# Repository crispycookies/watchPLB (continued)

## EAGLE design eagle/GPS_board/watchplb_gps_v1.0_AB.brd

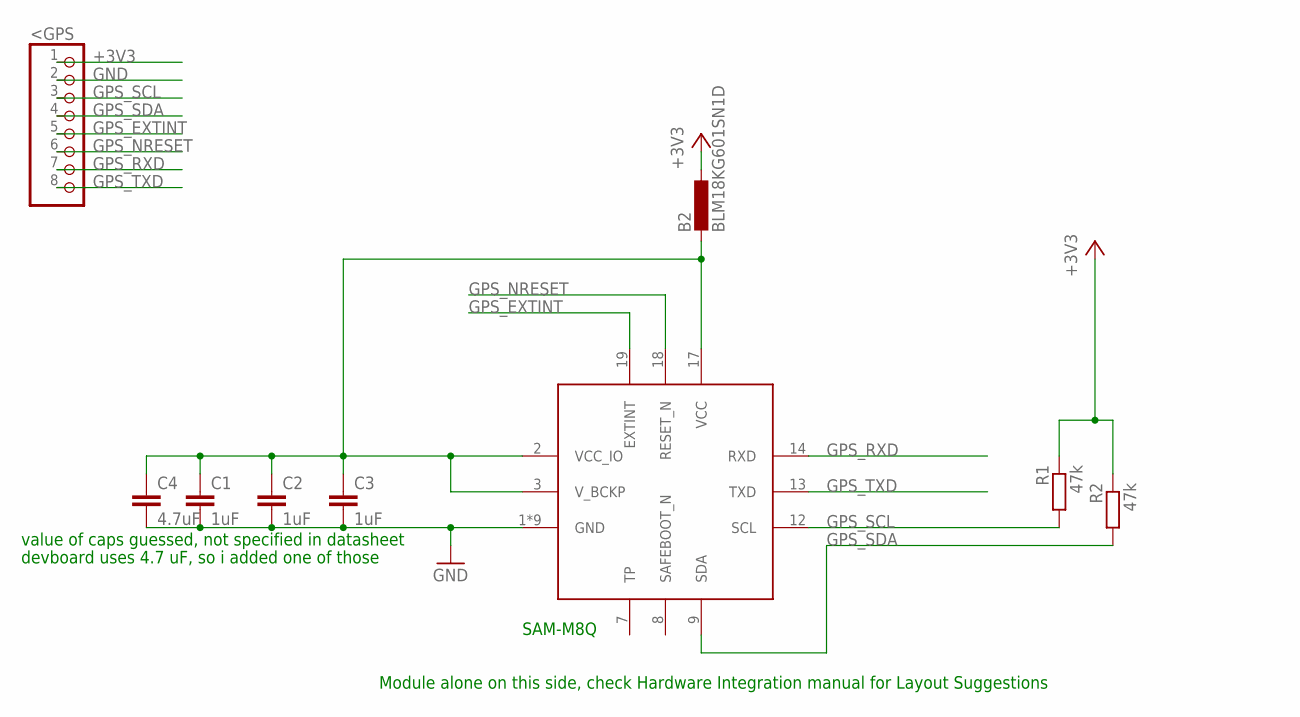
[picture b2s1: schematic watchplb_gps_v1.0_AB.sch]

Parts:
<GPS: PINHD-1X8; 1X08
B2: BLM18KG601SN1D; L0603
C1, C2, C3: 1uF; C0805
C4: 4.7uF; C0805
IC1: SAM-M8Q
R1, R2: 47k; M0805

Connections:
+3V3: <GPS.1, B2.1, R1.1, R2.1
GND: <GPS.2, C1.2, C2.2, C3.2, C4.2, IC1.1 (GND), IC1.4 (GND), IC1.5 (GND), IC1.6 (GND), IC1.10 (GND), IC1.11 (GND), IC1.15 (GND), IC1.16 (GND), IC1.20 (GND)
GPS_EXTINT: <GPS.5, IC1.19 (EXTINT)
GPS_NRESET: <GPS.6, IC1.18 (RESET_N)
GPS_RXD: <GPS.7, IC1.14 (RXD)
GPS_SCL: <GPS.3, IC1.12 (SCL), R1.2
GPS_SDA: <GPS.4, IC1.9 (SDA), R2.2
GPS_TXD: <GPS.8, IC1.13 (TXD)
unnamed: B2.2, C1.1, C2.1, C3.1, C4.1, IC1.2 (VCC_IO), IC1.3 (V_BCKP), IC1.17 (VCC)

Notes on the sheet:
Module alone on this side, check Hardware Integration manual for Layout Suggestions
value of caps guessed, not specified in datasheet
devboard uses 4.7 uF, so i added one of those
SAM-M8Q

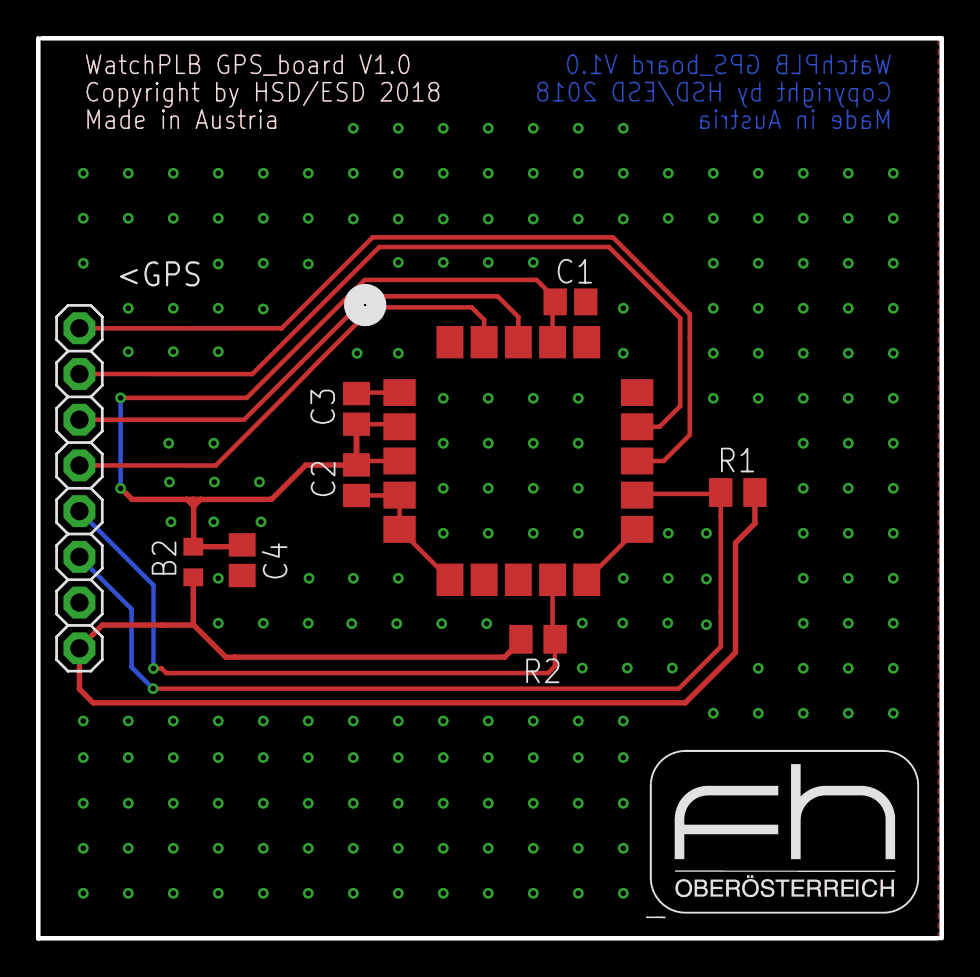
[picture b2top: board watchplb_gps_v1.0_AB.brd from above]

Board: 2 copper layers, 50.2 x 50.0 mm, 10 parts (0 on the bottom side), 9 nets.

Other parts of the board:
U$1: FH_LOGO_050

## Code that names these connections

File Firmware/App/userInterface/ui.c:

/**
 **************************
 * @file    ui.c
 * @author  Michael Neuhofer
 * @version V1.0
 * @date    18.12.2018
 * @brief   user interface module
 **************************
 */

#include <stdbool.h>

#include "ui.h"
#include "led_driver.h"
#include "sysclock_driver.h"
#include "vibrator_driver.h"
#include "key.h"
#include "emergencyCall.h"
#include "battery.h"
#include "adc.h"
#include <stdbool.h>


typedef enum {
	UI_Idle, UI_Waiting, UI_SendLocation, UI_Sleepmode
} UIstates;

UIstates UIstate = UI_Idle;
static bool isSleepmode = false;
static const TIME ledtimercd = 10;
static REGISTER ledreg = 0x0F;

const uint8_t battery_100 = 80;
const uint8_t battery_80 = 60;
const uint8_t battery_60 = 40;
const uint8_t battery_40 = 20;
const uint8_t battery_20 = 0;

const uint16_t limiter = 1000;
static uint16_t counter = 0;

void UI_UpdateBattery() {
	// Check Battery state via ADC
	uint8_t battery = battery_status();

	if (battery > battery_100 ) {
		led_on(led_pa4);
		led_on(led_pa5);
		led_on(led_pa6);
		led_on(led_pa7);
		led_on(led_pc4);
	} else if (battery > battery_80) {
		led_off(led_pa4);
		led_on(led_pa5);
		led_on(led_pa6);
		led_on(led_pa7);
		led_on(led_pc4);
	} else if (battery > battery_60) {
		led_off(led_pa4);
		led_off(led_pa5);
		led_on(led_pa6);
		led_on(led_pa7);
		led_on(led_pc4);
	} else if (battery > battery_40) {
		led_off(led_pa4);
		led_off(led_pa5);
		led_off(led_pa6);
		led_on(led_pa7);
		led_on(led_pc4);
	} else if (battery >= battery_20) {
		led_off(led_pa4);
		led_off(led_pa5);
		led_off(led_pa6);
		led_off(led_pa7);
		led_on(led_pc4);
	} else {
		_Error_Handler("statebatteryerror", 222);
	}

}

void UI_TurnLEDsOff() {
	led_off(led_pa4);
	led_off(led_pa5);
	led_off(led_pa6);
	led_off(led_pa7);
	led_off(led_pc4);
	led_off(led_pc5);
	led_off(led_pb0);
	led_off(led_pb1);
	led_off(led_pb2);
}

void UI_CrazyLEDs() {
	led_timer_start();
	led_action_time(led_pa4, ledreg);
	led_action_time(led_pa5, ledreg);
	led_action_time(led_pa6, ledreg);
	led_action_time(led_pa7, ledreg);
	led_action_time(led_pc4, ledreg);
//led_action_time(led_pc5,ledreg);
	led_action_time(led_pb0, ledreg);
	led_action_time(led_pb1, ledreg);
	led_action_time(led_pb2, ledreg);
//led_timer_stop();
}

HAL_StatusTypeDef UI_Init() {

	KEY_Init();

	led_init();
	battery_init();

	led_timer_init(ledtimercd);
//vibrator_init(GPIOA,15);
	UIstate = UI_Idle;

	return HAL_OK;
}

HAL_StatusTypeDef UI_Update() {


	if(counter >= limiter){
		UI_UpdateBattery();
		counter = 0;
	}
	counter++;


	switch (UIstate) {
	case UI_Idle: {

		UIstate = UI_Waiting;
		break;
	}
	case UI_Waiting: {

		led_on(led_pb1);

		if (KEY_Get(BTN_1) == GPIO_PIN_SET) {
			// Sleepmode
			UIstate = UI_Sleepmode;
		} else if (KEY_Get(BTN_2) == GPIO_PIN_SET) {
			// activate Bluetooth here ////////////////////////////////////////////////////////////////
			led_on(led_pb0); /////////////////////////////TEST PURPOSE
			UIstate = UI_Waiting;

		} else if (KEY_Get(BTN_3) == GPIO_PIN_SET) {
			if (KEY_Get(BTN_4) == GPIO_PIN_SET) {
				//SOS
				UIstate = UI_SendLocation;
			}
		}

		// show the battery status via LEDs
		//UI_UpdateBattery();

		break;
	}
	case UI_SendLocation: {
		//vibrator_on();
		// call SOS function

		EMC_SetEmergency(EMC_State_Emergency);

		//vibrator_off();
		led_on(led_pb2); /////////////////////////////TEST PURPOSE

		UIstate = UI_Waiting;
		break;
	}
	case UI_Sleepmode: {
		if (isSleepmode != true) {
			UI_TurnLEDsOff();
			isSleepmode = true;
			SystemClock_SleepMode_Config();
			// indicates Sleepmode
			led_on(led_pc5);
		}

		if (KEY_Get(BTN_2) == GPIO_PIN_SET || KEY_Get(BTN_3) == GPIO_PIN_SET
				|| KEY_Get(BTN_4) == GPIO_PIN_SET) {
			SystemClock_UnSleepMode_Config();
			UIstate = UI_Waiting;
			isSleepmode = false;
			led_off(led_pc5);
		}
		break;
	}
	default: {
		//errorhandler makes all LEDs go crazy
		_Error_Handler("stateerror", 222);
	}
	}

	return HAL_OK;
}

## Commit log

2018-03-06 Add .gitignore
2018-03-06 first version of specification
2018-04-03 initial upload schematic
2018-04-03 Add new directory
2018-04-03 initial commit schematic
2018-04-03 initial upload board
2018-04-03 Added Pflichtenheft Directory
2018-04-03 Uploaded Pflichtenheft.pdf
2018-04-03 Upload Pflichtenheft.tex
2018-04-03 antenna_calc
2018-04-03 Firmware init
2018-04-03 Updated Pflichtenheft.tex
2018-04-03 Updated Pflichtenheft.pdf
2018-04-06 added folder to git ignore
2018-04-17 added pdf version
2018-04-17 added testpoints, moved pins so pb11 is free to make it pin kompatibel to another prozessor with more power
2018-04-17 created directory structure
2018-04-17 no message
2018-04-18 finished directory structure
2018-04-18 finished makefile
2018-04-18 created specification
2018-04-18 added com interface
2018-04-18 mein benutzereigenschaften und hardwareschnittstellen
2018-04-18 Punkt 5 erledigt
2018-04-18 punkt 2.2 und 4 done
2018-04-19 imported olgas specification changes
2018-04-19 Added Pflichtenheft
2018-04-19 Replaced Specification as it failed last time
2018-04-19 pflichenheft änderungen: alles bei punkt 2, ausser 2.1.3, 2.1.4 und 2.2 und punkt 3
2018-04-20 meine änderungen
2018-04-20 merged specifications
2018-04-20 Removed Contradictoriness
2018-04-20 added PCB acronym list
2018-04-24 added wakeup pin support and page for psu (empty atm)
2018-04-24 added auto-generated BOM
2018-04-24 added gitignore for eagle
2018-04-24 include stm32l0xx_hal_conf.h in all files
2018-04-24 added mouser numbers for most products, changed switches to smd
2018-04-24 changed mosfet to one with sot23 footprint
2018-04-24 added new mosfet to bom
2018-04-24 Template for EVA
2018-04-24 Upload Lights Template for EVA
2018-05-06 started on uart implementation
2018-05-08 USB-VCOM generated with cubemx and changed to send useful message
2018-05-08 added VCOM usb port with protection
2018-05-09 implemented most uart routines. TODO: DMA and interrupts
2018-05-15 fixed lowercase app directory to uppercase App
2018-05-15 added RF transmitter (amp still missing) and generated new pdf of schematic for tobi
2018-05-15 added rf amp and sma connector, reorganised for better pdf page ordering
2018-05-16 fixed makefile to also work on Linux
2018-05-16 Untested LED- Driver-Compileable
2018-05-16 Untested Led- Driver- Full Project
2018-05-16 Fixed Directory Struct
2018-05-16 Removed Folders
2018-05-16 added battery protection circuit
2018-05-22 added calculations as excel file and battery charge circuitry in schematic
2018-05-22 Added Vibrator and removed uselessenum in led driver
2018-05-26 added linear regulators + calculations for them, exported parts as library, generated new pdf
2018-05-26 added 4.7uF to gps module because the devboard does that.
2018-05-27 added dma interrupt module
2018-05-27 worked on uart driver: worked on dma implementation
2018-05-28 compile uart module instead of usart, compile uart extension
2018-05-28 configure interrupt priority
2018-05-28 implemented start transmission and interrupts and
2018-05-29 implemented receiver
2018-05-29 added error returns added uart receive idle line detection
2018-05-29 added missing names + new pdf
2018-05-29 switched to cubeMx cmsis driver
2018-05-29 small schematic changes, started with layout
2018-06-05 keyTreiber getestet und funktionsfählig
    adc not finished so far
2018-06-05 added some datasheets and continued with layout
2018-06-05 Fixed Led- Driver. Timer may be too Fast
2018-06-05 Fixed Led Driver Constants
2018-06-05 continued layout
2018-06-06 added necessary components
2018-06-06 enable dma interrupts
2018-06-06 reset data of all handlers to prevent errors by initial values
2018-06-06 enable dma clock and USART interrupt
2018-06-06 set usart instance before initialisation
2018-06-06 clear correct interrupt
2018-06-06 clear initial idle interrupt and enable idle interrupts
2018-06-06 addec test routine for the uart module
2018-06-12 layout v1 fertig
2018-06-12 Final LED- Driver Rework
    Added Documentation in Code and fixed Interrupt Bug
2018-06-12 Doxygen Documentation
    Finalized Doxygen Documentation for Vibrator/forceFeedback
2018-06-12 adc / key fertig
2018-06-12 added text and fh logo
2018-06-12 watchdog implementiert nicht getestet
2018-06-19 SPI Driver Untested
    Untested and Probably doesnt work either...
2018-06-19 changes requested by armin brandl
2018-06-19 SPI Driver Untested and Merged
2018-06-19 fixed uart
2018-06-22 weitere Änderungen von Armin Brandl
2018-07-11 von Armin überarbeitete Version der GPS-Platine
2018-07-11 Änderungen laut Besprechung mit Armin (soweit ich mich erinnern kann, ist schon ne woche her)
2018-07-11 SPI Driver Tested on APUS
2018-07-17 fixed copy paste error
2018-07-18 kleine Änderungen laut email mit Armin, veraltete Dateien entfernt, gerber generiert
2018-07-18 modified gitignore so gerber files get committed too
2018-07-19 added comments and additional checks against null- pointer
2018-07-19 added comments
2018-07-20 started BOM
2018-07-26 BOMs finished, requesting feedback from Armin Brandl
2018-07-27 changes to BOM as requested by Armin Brandl
2018-07-27 small changes
2018-09-04 Added Files for use with SmtAssistant
2018-09-24 Removed NUL- File
2018-09-24 Untested Bugfixed for SPI
2018-09-29 Marked received Parts on BOM
2018-09-29 Noticed that I forgot to apply the Calculations for Linear Voltage Regulators to eagle, fixed this
2018-10-02 Formular for test PLB
2018-10-03 removed unnecessary extern inclusions
2018-10-03 deleted file 'NUL'
2018-10-03 fixed directories: removed debug folder, merged app folder into App
2018-10-05 Proposal for BLE- Interface
2018-10-05 Removed Useless Array in SPI.c
2018-10-09 adc+watchdog fertig und kommentiert
2018-10-09 added nmea gpgll implementation
2018-10-09 fixed filename, updated makefile, fixed compile errors
2018-10-09 LED Hotfix
2018-10-09 plb_modulate_send_data
2018-10-09 Added Mask
2018-10-15 small schematic changes
2018-10-27 added nmea position callback
2018-10-27 implemented ubx protocol base
2018-11-06 added Position interface
2018-11-06 added location module
2018-11-07 added valid flag to Position struct
2018-11-07 finished location module
2018-11-07 implemented location in main
2018-11-07 plb.h
2018-11-09 removed redundant message init
2018-11-09 compare against the class and id in the payload instead of ack class and id
2018-11-09 documented ubx module
2018-11-09 documented position interface
2018-11-12 use toLower from ctype
2018-11-12 added documentation for nmea module
2018-11-13 Added Function to compare time sto position module
2018-11-13 Added BitArray module
2018-11-13 Added PLB module from Olga
2018-11-13 Added emergency call module
2018-11-13 created simple led and buttons demo
2018-11-14 Enable charging Pin
2018-11-14 changed values for I/Q modulator
2018-11-19 fixed path upper/lower case for main
2018-11-19 Added usb driver
2018-11-19 added log module
2018-11-20 Fix key driver
2018-11-20 Add CRC- Directory
2018-11-20 Upload CRC 8 File
2018-11-20 remove unnecessary files
2018-11-20 fixed function spelling
2018-11-20 Fixed data transmitting
2018-11-20 Improve SPI driver
2018-11-20 update for spi driver changes
2018-11-22 use 10-Bit values for modulation
2018-11-23 recompile on include file change
2018-11-23 add necessary libraries
2018-11-23 fix function name
2018-11-24 Revert "Update ble_interface.c"
    This reverts commit cb3aec1413bc6a20185946dbc1a3e6f8539799c3.
2018-11-24 BLE Hotfix
2018-11-24 reduced plb module to creating the frame: - moved most functions to emc and radio modules - moved transmitting functions from emc to radio - emc updates frames on changes between transmissions
2018-11-28 USB + log funktionsfähig und getestet
2018-11-30 Fixed indentation in logger use macro for buffer length use vsnprintf instead of vsprintf check if initialized removed unnecessary return values
2018-11-30 moved usb module to user driver
2018-11-30 Moved USB interrupts to usb driver
2018-12-01 Removed uneccessary file
2018-12-01 Merged main function
2018-12-01 specify format as char
2018-12-01 Removed unnecessary files (already contained in CMSIS)
2018-12-01 readded necessary initialization
2018-12-02 added logger interface
2018-12-02 added pos to string function
2018-12-02 moved pos to string to logger as LOG_POS
2018-12-02 added bitarray logging
2018-12-02 Added log to emc module
2018-12-03 replaced magic number with existing macro
2018-12-03 Added missing function prototype in loc header
2018-12-03 worked on radio module to at least simulate transmission
2018-12-03 added injection of locations
2018-12-03 created test routine
2018-12-03 added data modulation
2018-12-03 added logging of transmitting data
2018-12-03 added location process call
2018-12-03 disable uart and spi for demo
2018-12-04 Added divider for minutes
2018-12-04 more logs
2018-12-04 add commentary for N/S and E/W flags
2018-12-04 tb for protocol
2018-12-04 LED and SPI Hotfix
2018-12-05 Clear last Pos update timestamp in init
2018-12-05 improve test routine
2018-12-05 Improve bitarray logging
2018-12-06 fix IQ_0
2018-12-06 fix signs
2018-12-06 Fix flag enum value in position for plb
2018-12-06 reduce prezistion from double to float
2018-12-06 Add delay to prevent log messages get discarded because USB isn't ready
2018-12-06 Fix radio state machine
2018-12-06 add position logging on injected position
2018-12-06 Improve radio SetFrame function
2018-12-10 added time comparison, added position to string function
2018-12-10 fix state transitions and add logs
2018-12-10 fix makefile and remove HAL_Delay
2018-12-11 Accumulated Changes over a few weeks
2018-12-18 Sysclock Package
2018-12-18 einige kleine Änderungen: mcp111 ist smd massen verbinden taster footprint richtig orientierungspunkt U5 BQ ding richtungsmarkierung bei diode im Bat prot reset leitung bei pin verbinden LED rs auf 4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
2018-12-18 sysclock driver
2018-12-18 added include in makefile
2018-12-18 added radio configuration extended statemachine
2019-01-08 User Interface Treiber WIP
2019-01-08 Updated Sysclock Driver
2019-01-08 + started doku
2019-01-12 new demo programm
2019-01-12 fixed uart gpio pins for location
2019-01-14 remove nano.specs for full scanf
2019-01-14 add function to configure nmea messages
2019-01-14 fix checksum
2019-01-14 remove unnecessary include (stdint is global include)
2019-01-14 Add callback for other messages
2019-01-14 fix spelling error
2019-01-14 add more message types
2019-01-14 add trailing zero to data buffer
2019-01-14 fix check of too large messages
2019-01-14 configure gps module
2019-01-14 fix message logging
2019-01-14 fix main file
2019-01-14 also call ubx, nmea
2019-01-15 statemachine updated
2019-01-15 Debug BLE Driver
2019-01-15 Battery Status implementation in UI
2019-01-15 demo app
2019-01-15 new frequency settings
2019-01-15 adc updated
2019-01-22 adc tested
2019-01-22 radio fixxes
2019-01-22 Batterie + adc working/tested
2019-01-22 Patch for Michi
2019-01-24 fixed radio statemachine
2019-01-24 fix transmit return value
2019-01-24 rename rec to status
2019-01-24 add getreg function
2019-01-24 add radio memory dump
2019-01-24 add loggin over uart-usb
2019-01-24 Patched Battery Driver
2019-01-24 fixed parameter
2019-01-25 plakat
2019-01-25 added logging over gps uart port
2019-01-25 To be stashed
2019-01-29 don't init loc
2019-01-29 set usb logging
2019-01-29 fix spi bit ordering
2019-01-29 fix radio configuration
2019-01-29 disable cs in spi init
2019-01-29 fix radio status masks
2019-01-29 send message with interval
2019-02-03 SPI Rework
2019-02-03 SPI Refactoring
2019-02-03 ForceFeedback Refactoring
2019-02-05 continued doku
2019-02-11 created documentation
2019-02-14 created main file
2019-02-14 fixed compiler warning
2019-02-14 finished my documentation
2019-02-20 created doxyfile and added logo
2019-02-20 fix file header
2019-02-20 exclude markdown files and CMSIS and HAL driver from doxygen
2019-06-16 Create LICENSE
